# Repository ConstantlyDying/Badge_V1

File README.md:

# Badge_V1
A simple PCB Badge with NFC and an E ink DIsplay!

Its made with a SEEED XIAO ESP_32_C3 :p, a 2.9inch E_ink display with its driver board, NFC (ST25DV04K), and NeoPixels!!.

## What it does

It can show your picture and name (the usual stuff), it can also toggle between social media or different profiles depending on what event you are at with a push of a button (can also be wirelessly controlled:D). It also contains a halo of NeoPixels which make a cool underglow and can react to the NFC or can be configured to do other fun stuff (ex: diff lighting modes for each profile). The NFC part of the badge can store multiple URL's for each social media acc or whatever it is you want it to do (toggled by a push of a button).  It can also be controlled via bluetooth as the MC im using is bluetooth enabled

After attending a hackathon (Fallout), I saw @KaiPereira with his version of a REALLLLLY COOL PCB Badge and decided I wanted one too, I mean why not. So I made this simpler version with a ready-made microcontroller. Now I can have a badge of my own. And yeah, it has lots of scope for improvement, its my first badge after all, and I was in quite a time constraint while making this :).

## BOM
| Item | Quantity | Cost (INR) | Cost (USD) |
|---|---:|---:|---:|
| E ink display | 1 | 1700 | 17 |
| Xiao ESP32-C3 | 1 | 800 | 8 |
| Screws | 6–7 | 300 | 3 |
| PCB Fab + PCBA | 1 | 5000 | ~50 |
| **Total** |  | **7800** | **78** |

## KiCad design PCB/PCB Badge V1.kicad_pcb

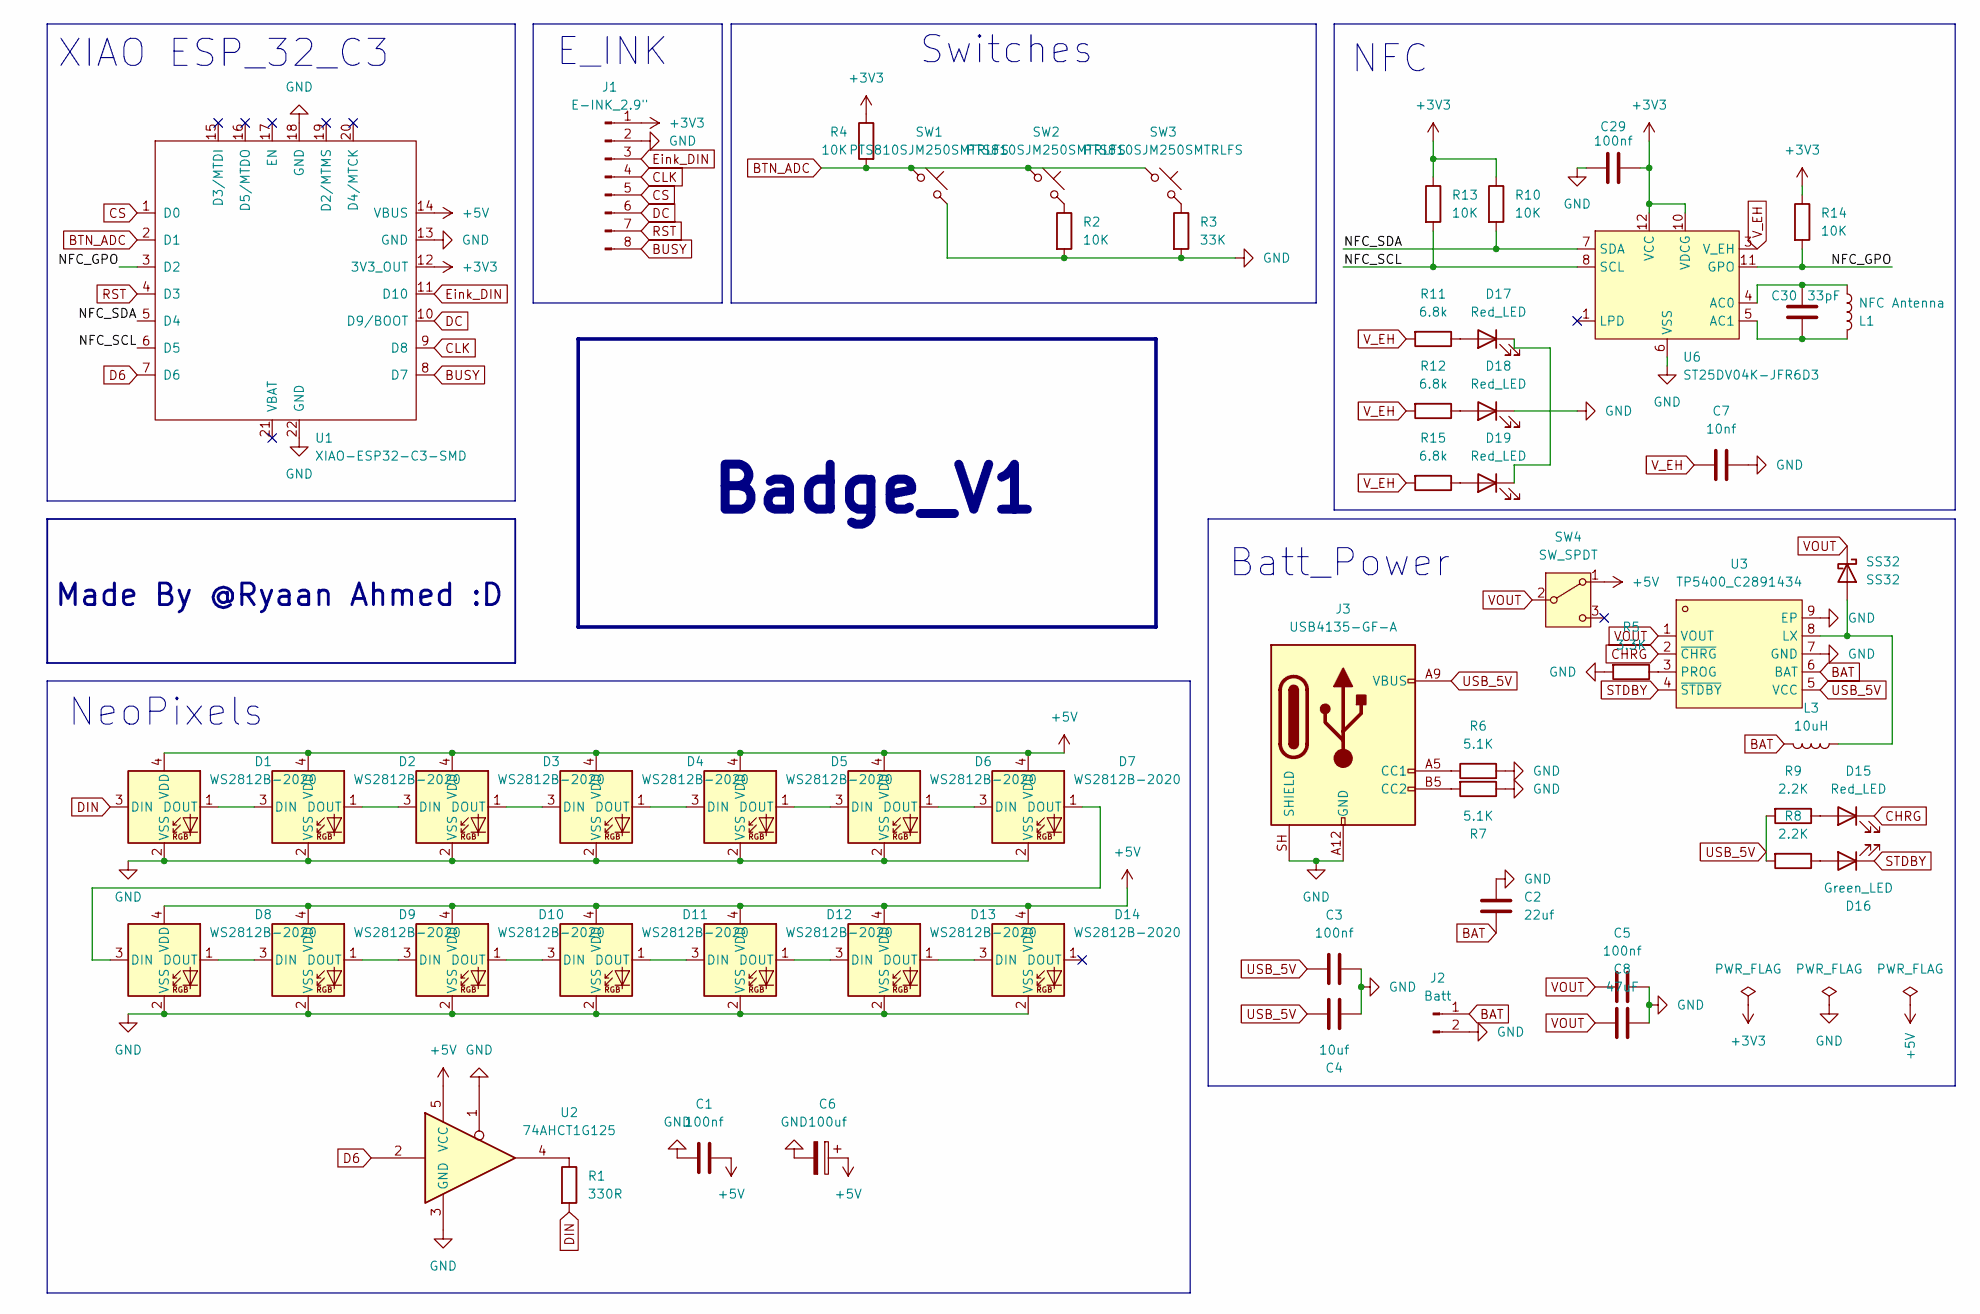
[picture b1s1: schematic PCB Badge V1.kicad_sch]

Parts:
C1, C3, C5, C29: 100nf; C0402
C2: 22uf; C_0805_2012Metric
C4: 10uf; C_0603_1608Metric
C6: 100uf; C1210
C7: 10nf; C_0402_1005Metric
C8: 47uF; C1206
C30: 33pF; C0402
D1, D2, D3, D4, D5, D6, D7, D8, D9, D10, D11, D12, D13, D14: WS2812B-2020; LED-SMD_4P-L2.0-W2.0-BR-1
D15, D17, D18, D19: Red_LED; LED_0402_1005Metric
D16: Green_LED; LED-SMD_L1.0-W0.5_FC-F1005UGK
J1: E-INK_2.9"; PinHeader_1x08_P2.54mm_Vertical
J2: Batt; PinHeader_1x02_P2.54mm_Vertical_SMD_Pin1Left
J3: USB4135-GF-A; USB_C_Receptacle_GCT_USB4135-GF-A_6P_TopMnt_Horizontal
L1: NFC Antenna; 25x35mm-NFC
L3: 10uH; IND-SMD_L4.0-W4.0_XAL4040
R1: 330R; R0402
R2, R4, R10, R13, R14: 10K; R0402
R3: 33K; R0402
R5: 3.3K; R0402
R6, R7: 5.1K; R0402
R8, R9: 2.2K; R0402
R11, R12, R15: 6.8k; R0402
SS32: SS32; SMA_L4.3-W2.6-LS5.2-RD
SW1, SW2, SW3: PTS810SJM250SMTRLFS; SW-SMD_4P_PTS810SJM250SMTRLFS
SW4: SW_SPDT; SW-SMD_MK-12C02-G020
U1: XIAO-ESP32-C3-SMD
U2: 74AHCT1G125; SOT-23-5
U3: TP5400_C2891434; ESOP-8_L4.9-W3.9-P1.27-LS6.0-BL-EP; MPN TP5400; LCSC Part C2891434
U6: ST25DV04K-JFR6D3; ST_UFDFPN-12-1EP_3x3mm_P0.5mm_EP1.4x2.55mm

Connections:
+3V3: C29.2, J1.1, R4.1, R10.1, R13.1, R14.1, U1.12 (3V3_OUT), U6.10 (VDCG), U6.12 (VCC)
+5V: C1.1, C6.1, D1.4 (VDD), D2.4 (VDD), D3.4 (VDD), D4.4 (VDD), D5.4 (VDD), D6.4 (VDD), D7.4 (VDD), D8.4 (VDD), D9.4 (VDD), D10.4 (VDD), D11.4 (VDD), D12.4 (VDD), D13.4 (VDD), D14.4 (VDD), SW4.1 (A), U1.14 (VBUS), U2.5 (VCC)
/NFC_GPO: R14.2, U1.3 (D2), U6.11 (GPO)
/NFC_SCL: R13.2, U1.6 (D5), U6.8 (SCL)
/NFC_SDA: R10.2, U1.5 (D4), U6.7 (SDA)
BAT: C2.2, J2.1, L3.2, U3.6 (BAT)
BTN_ADC: R4.2, SW1.1, SW2.1, SW3.1, U1.2 (D1)
BUSY: J1.8, U1.8 (D7)
CHRG: D15.1 (K), U3.2 (~CHRG)
CLK: J1.4, U1.9 (D8)
CS: J1.5, U1.1 (D0)
D6: U1.7 (D6), U2.2
DC: J1.6, U1.10 (D9/BOOT)
DIN: D1.3 (DIN), R1.2
Eink_DIN: J1.3, U1.11 (D10)
unnamed: D1.1 (DOUT), D2.3 (DIN)
unnamed: D2.1 (DOUT), D3.3 (DIN)
unnamed: D3.1 (DOUT), D4.3 (DIN)
unnamed: D4.1 (DOUT), D5.3 (DIN)
unnamed: D5.1 (DOUT), D6.3 (DIN)
unnamed: D6.1 (DOUT), D7.3 (DIN)
unnamed: D7.1 (DOUT), D8.3 (DIN)
unnamed: D8.1 (DOUT), D9.3 (DIN)
unnamed: D9.1 (DOUT), D10.3 (DIN)
unnamed: D10.1 (DOUT), D11.3 (DIN)
unnamed: D11.1 (DOUT), D12.3 (DIN)
unnamed: D12.1 (DOUT), D13.3 (DIN)
unnamed: D13.1 (DOUT), D14.3 (DIN)
unnamed: D15.2 (A), R9.1
unnamed: D16.2 (A), R8.1
unnamed: D17.2 (A), R11.1
unnamed: D17.1 (K), D19.1 (K)
unnamed: D18.2 (A), R12.1
unnamed: D19.2 (A), R15.1
unnamed: J3.A5 (CC1), R6.1
unnamed: J3.B5 (CC2), R7.2
unnamed: R1.1, U2.4
unnamed: R2.1, SW2.2
unnamed: R3.1, SW3.2
unnamed: L3.1, SS32.2 (A), U3.8 (LX)
unnamed: R5.1, U3.3 (PROG)
unnamed: C30.2, L1.2, U6.4 (AC0)
unnamed: C30.1, L1.1, U6.5 (AC1)
RST: J1.7, U1.4 (D3)
STDBY: D16.1 (K), U3.4 (~STDBY)
USB_5V: C3.2, C4.2, J3.A9 (VBUS), J3.B9 (VBUS), R8.2, R9.2, U3.5 (VCC)
V_EH: C7.2, R11.2, R12.2, R15.2, U6.3 (V_EH)

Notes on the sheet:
Switches
Made By @Ryaan Ahmed :D
Badge_V1
NeoPixels
XIAO ESP_32_C3
E_INK
NFC
Batt_Power

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
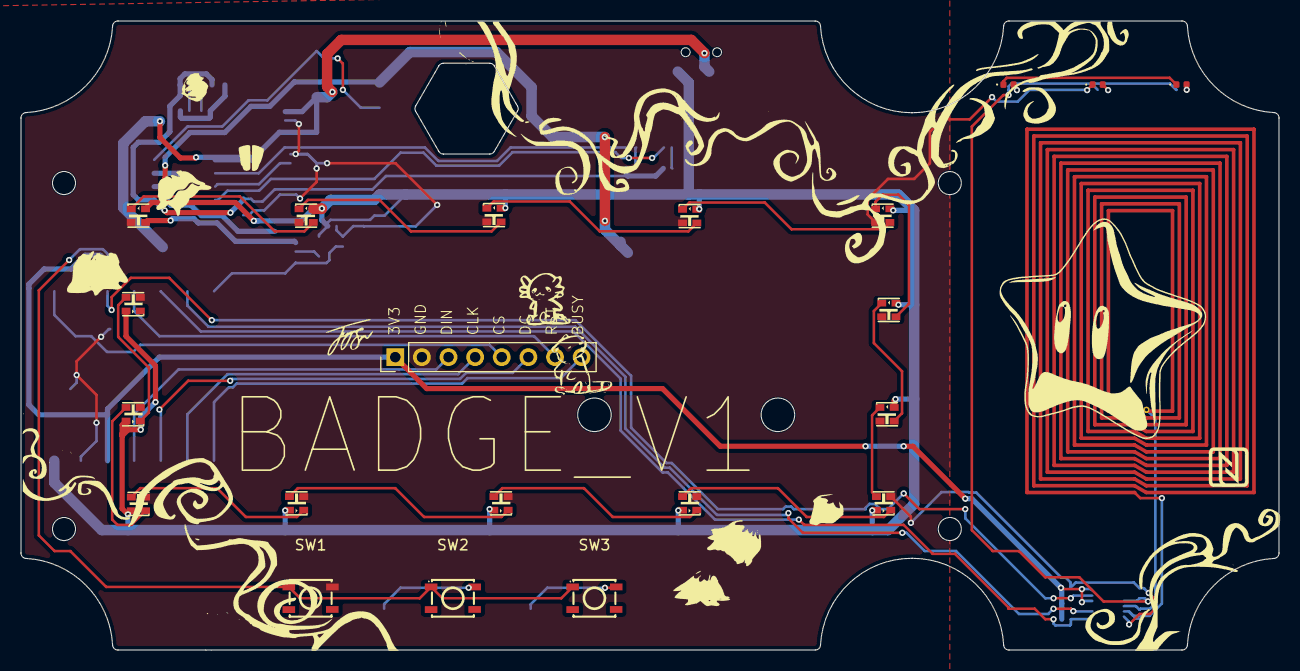
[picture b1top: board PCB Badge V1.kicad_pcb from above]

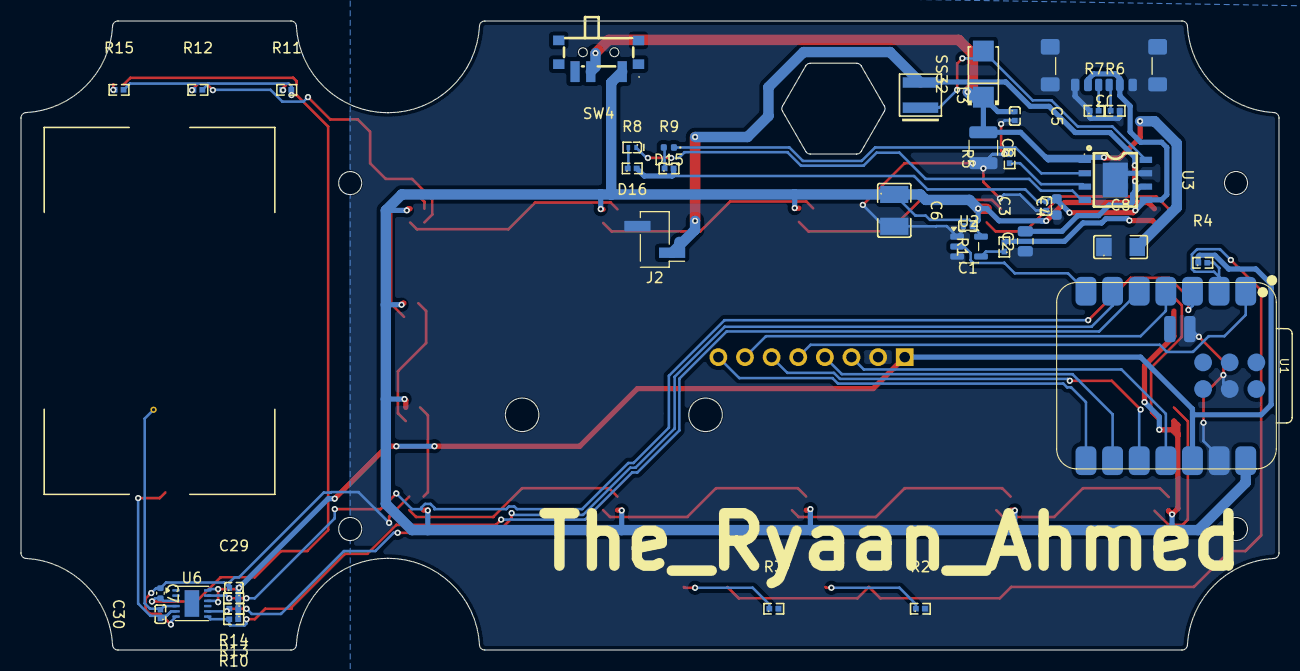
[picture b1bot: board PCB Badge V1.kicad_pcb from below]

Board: 2 copper layers, 120.0 x 60.0 mm, 59 parts (37 on the bottom side), 49 nets.

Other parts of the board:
C8#2: 47uF; C1206

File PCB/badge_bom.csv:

Designator,Footprint,Quantity,Value,LCSC Part #
"C1, C29, C3, C5",C0402,4,100nf,C106204
C2,0805,1,22uf,
C30,C0402,1,33pF,C106204
C4,0603,1,10uf,
C6,C1210,1,100uf,C49066
C7,0402,1,10nf,
C8_2,C1206,1,47uF,C92821
C8,1210,1,C_Polarized,
"D1, D10, D11, D12, D13, D14, D2, D3, D4, D5, D6, D7, D8, D9",LED-SMD_4P-L2.0-W2.0-BR-1,14,WS2812B-2020,C5349955
"D15, D17, D18, D19",0402,4,Red_LED,
D16,LED-SMD_L1.0-W0.5_FC-F1005UGK,1,Green_LED,C130723
J3,USB_C_Receptacle_GCT_USB4135-GF-A_6P_TopMnt_Horizontal,1,USB4135-GF-A,
L1,25x35mm-NFC,1,NFC Antenna,
L3,IND-SMD_L4.0-W4.0_XAL4040,1,10uH,C5144883
R1,R0402,1,330R,C156119
"R10, R13, R14, R2, R4",R0402,5,10K,C156119
"R11, R12, R15",R0402,3,6.8k,C156119
R3,R0402,1,33K,C156119
R5,R0402,1,3.3K,C156119
"R6, R7",R0402,2,5.1K,C156119
"R8, R9",R0402,2,2.2K,C156119
SS32,SMA_L4.3-W2.6-LS5.2-RD,1,SS32,C34897
"SW1, SW2, SW3",SW-SMD_4P_PTS810SJM250SMTRLFS,3,PTS810SJM250SMTRLFS,C221895
SW4,SW-SMD_MK-12C02-G020,1,SW_SPDT,C963206
U2,SOT-23-5,1,74AHCT1G125,
U3,ESOP-8_L4.9-W3.9-P1.27-LS6.0-BL-EP,1,TP5400_C2891434,C2891434
U6,ST_UFDFPN-12-1EP_3x3mm_P0.5mm_EP1.4x2.55mm,1,ST25DV04K-JFR6D3,
